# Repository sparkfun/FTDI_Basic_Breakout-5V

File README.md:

SparkFun FTDI Basic Breakout-5V
===============================

[*SparkFun FTDI Basic Breakout-5V(DEV-09716)*](https://www.sparkfun.com/products/9716)

This is a basic breakout board for the FTDI FT232RL USB to serial IC. 
The pinout of this board matches the FTDI cable to work with official Arduino and cloned Arduino boards. 
It can also be used for general serial applications. The major difference with this board is that it brings out the DTR pin as opposed to the RTS pin of the FTDI cable. 
The DTR pin allows an Arduino target to auto-reset when a new Sketch is downloaded. This is a really nice feature to have and allows a sketch to be downloaded without having to hit the reset button. 
This board will auto reset any Arduino board that has the reset pin brought out to a 6-pin connector.

Repository Contents
-------------------
* **/Hardware** - All Eagle design files (.brd, .sch)
* **/Production** - Test bed files and production panel files

Documentation
--------------

* **[Fritzing Part](https://github.com/sparkfun/Fritzing_Parts/blob/main/products/9716_sfe_ftdi_basic_breakout_5V_ft232rl.fzpz)** - Fritzing diagrams for SparkFun products.
* **[3D Model](https://github.com/sparkfun/3D_Models/tree/master/products/9716)**
* **[USB to Serial UART Boards Hookup Guide](https://learn.sparkfun.com/tutorials/sparkfun-usb-to-serial-uart-boards-hookup-guide)**
* **[How to Install FTDI Drivers](https://learn.sparkfun.com/tutorials/how-to-install-ftdi-drivers)**

 Product Versions
----------------
* [DEV-09716](https://www.sparkfun.com/products/9716)- 5V FTDI Basic Breakout
* [DEV-09873](https://www.sparkfun.com/products/9873)- 3.3V FTDI Basic Breakout

License Information
-------------------
The hardware is released under [Creative Commons ShareAlike 4.0 International](https://creativecommons.org/licenses/by-sa/4.0/).

Distributed as-is; no warranty is given.

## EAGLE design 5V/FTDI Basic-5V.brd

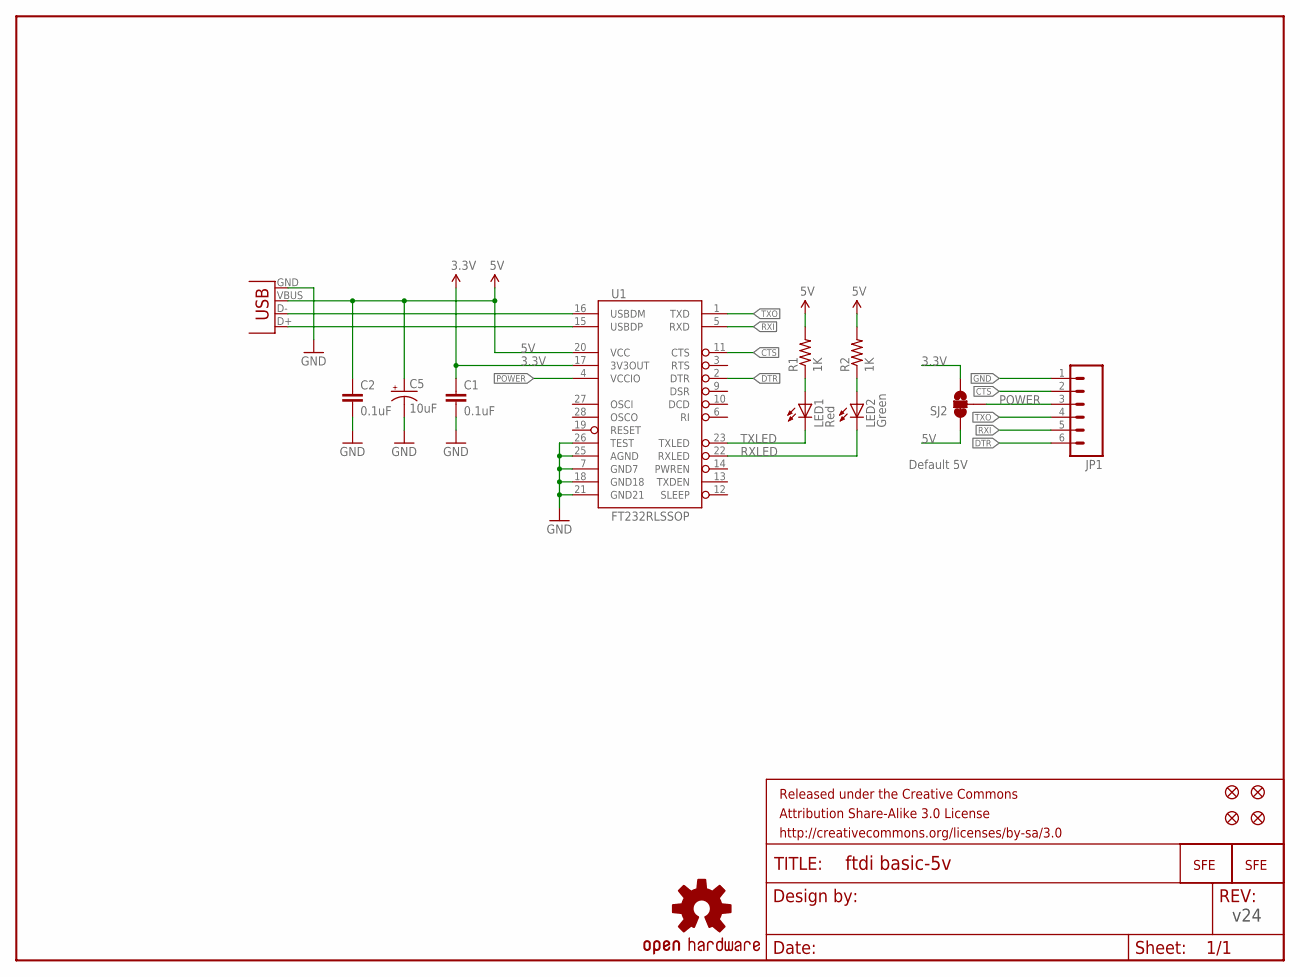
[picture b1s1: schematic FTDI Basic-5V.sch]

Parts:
C1, C2: 0.1uF; 0603-CAP
C5: 10uF; EIA3216
FRAME1: FRAME-LETTER; CREATIVE_COMMONS
JP1: M06SMD-FEMALE-V2; 1X06-SMD-FEMALE-V2
JP2: LOGO-SFESK; SFE-LOGO-FLAME
JP3, JP4, JP5, JP6: FIDUCIAL1X2; FIDUCIAL-1X2
LED1: Red; LED-0603
LED2: Green; LED-0603
LOGO1: OSHW-LOGOS; OSHW-LOGO-S
R1, R2: 1K; 0603-RES
SJ2: SOLDERJUMPER_2WAYS; SJ_3
U1: FT232RLSSOP; SSOP28DB
U$2: LOGO-SFENW2; SFE-NEW-WEB
X2: USB-SMD-NS; USB-MINIB-NOSTOP

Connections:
3.3V: C1.1, SJ2.3, U1.17 (3V3OUT)
5V: C2.1, C5.A (+), R1.2, R2.2, SJ2.1, U1.20 (VCC), X2.VBUS
CTS: JP1.2, U1.11 (CTS)
DTR: JP1.6, U1.2 (DTR)
GND: C1.2, C2.2, C5.C (-), JP1.1, U1.7 (GND7), U1.18 (GND18), U1.21 (GND21), U1.25 (AGND), U1.26 (TEST), X2.GND
unnamed: LED1.A, R1.1
unnamed: LED2.A, R2.1
POWER: JP1.3, SJ2.2, U1.4 (VCCIO)
RXI: JP1.5, U1.5 (RXD)
RXLED: LED2.C, U1.22 (RXLED)
TXLED: LED1.C, U1.23 (TXLED)
TXO: JP1.4, U1.1 (TXD)
USB_D+: U1.15 (USBDP), X2.D+
USB_D-: U1.16 (USBDM), X2.D-

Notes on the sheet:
Default 5V
v24

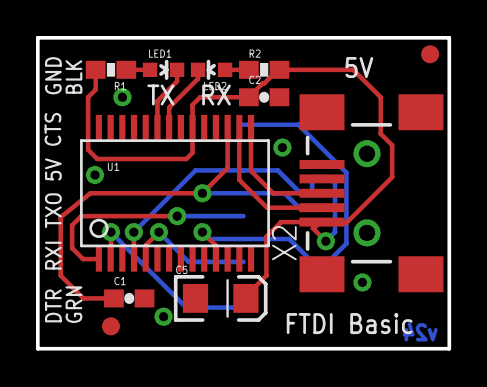
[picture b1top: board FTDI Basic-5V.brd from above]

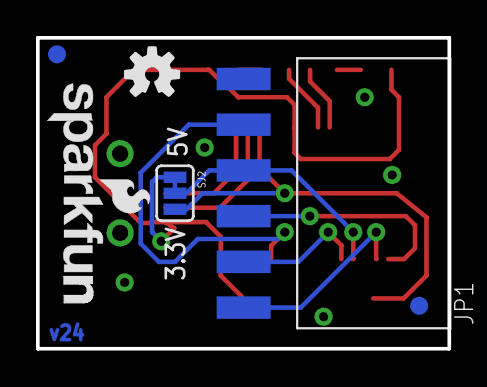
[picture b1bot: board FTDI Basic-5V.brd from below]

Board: 2 copper layers, 22.9 x 17.3 mm, 19 parts (7 on the bottom side), 14 nets.

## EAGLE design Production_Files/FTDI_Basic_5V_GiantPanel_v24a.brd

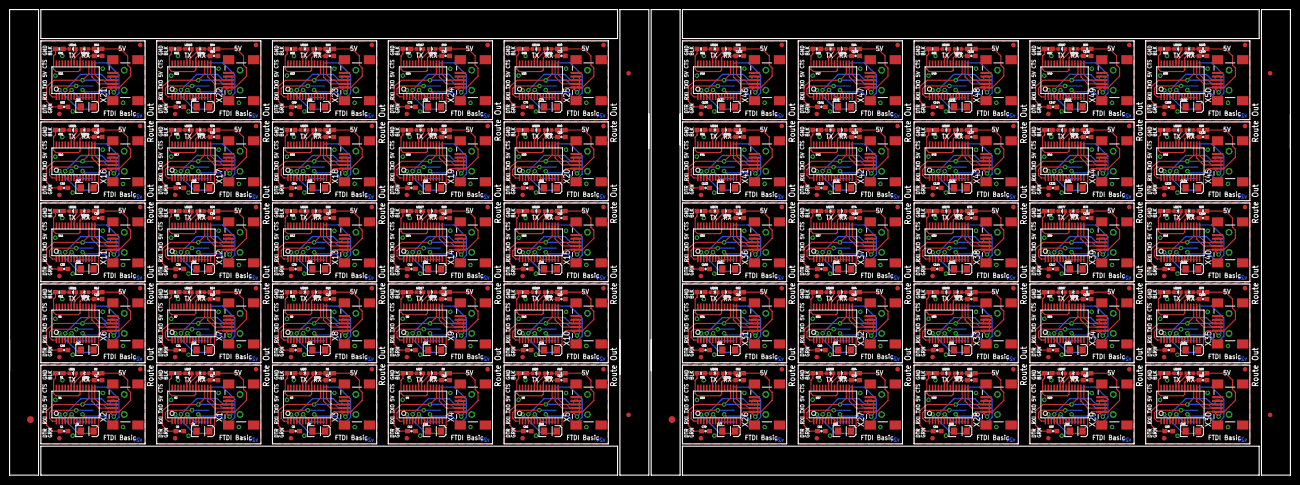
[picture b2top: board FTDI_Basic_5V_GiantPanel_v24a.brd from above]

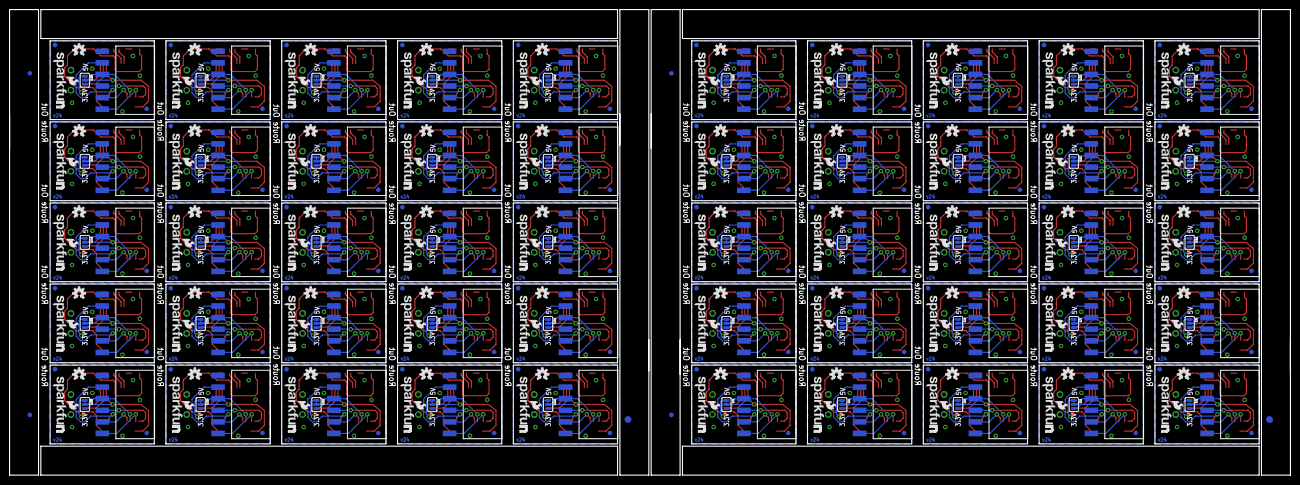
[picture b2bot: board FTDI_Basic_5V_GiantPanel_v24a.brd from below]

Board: 2 copper layers, 280.9 x 102.1 mm, 912 parts (356 on the bottom side), 700 nets.

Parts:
C1, C2, C3, C6, C7, C9, C10, C12, C13, C15, C16, C18, C19, C21, C22, C24, C25, C27, C28, C30, C31, C33, C34, C36, C37, C39, C40, C42, C43, C45, C46, C48, C49, C51, C52, C54, C55, C57, C58, C60, C61, C63, C64, C66, C67, C69, C70, C72, C73, C75, C76, C78, C79, C81, C82, C84, C85, C87, C88, C90, C91, C93, C94, C96, C97, C99, C100, C102, C103, C105, C106, C108, C109, C111, C112, C114, C115, C117, C118, C120, C121, C123, C124, C126, C127, C129, C130, C132, C133, C135, C136, C138, C139, C141, C142, C144, C145, C147, C148, C150: 0.1uF; 0603-CAP
C4, C5, C8, C11, C14, C17, C20, C23, C26, C29, C32, C35, C38, C41, C44, C47, C50, C53, C56, C59, C62, C65, C68, C71, C74, C77, C80, C83, C86, C89, C92, C95, C98, C101, C104, C107, C110, C113, C116, C119, C122, C125, C128, C131, C134, C137, C140, C143, C146, C149: 10uF; EIA3216
E$1, E$2, E$9, E$10: FIDUCIAL-1.5X3
E$3, E$4, E$5, E$6, E$7, E$8, E$11, E$12: FIDUCIAL-1X2
JP1, JP8, JP14, JP20, JP26, JP32, JP38, JP44, JP50, JP56, JP62, JP68, JP74, JP80, JP86, JP92, JP98, JP104, JP110, JP116, JP122, JP128, JP134, JP140, JP146, JP152, JP158, JP164, JP170, JP176, JP182, JP188, JP194, JP200, JP206, JP212, JP218, JP224, JP230, JP236, JP242, JP248, JP254, JP260, JP266, JP272, JP278, JP284, JP290, JP296: 1X06-SMD-FEMALE-V2
JP2, JP7, JP13, JP19, JP25, JP31, JP37, JP43, JP49, JP55, JP61, JP67, JP73, JP79, JP85, JP91, JP97, JP103, JP109, JP115, JP121, JP127, JP133, JP139, JP145, JP151, JP157, JP163, JP169, JP175, JP181, JP187, JP193, JP199, JP205, JP211, JP217, JP223, JP229, JP235, JP241, JP247, JP253, JP259, JP265, JP271, JP277, JP283, JP289, JP295: LOGO-SFESK; SFE-LOGO-FLAME
JP3, JP4, JP5, JP6, JP9, JP10, JP11, JP12, JP15, JP16, JP17, JP18, JP21, JP22, JP23, JP24, JP27, JP28, JP29, JP30, JP33, JP34, JP35, JP36, JP39, JP40, JP41, JP42, JP45, JP46, JP47, JP48, JP51, JP52, JP53, JP54, JP57, JP58, JP59, JP60, JP63, JP64, JP65, JP66, JP69, JP70, JP71, JP72, JP75, JP76, JP77, JP78, JP81, JP82, JP83, JP84, JP87, JP88, JP89, JP90, JP93, JP94, JP95, JP96, JP99, JP100, JP101, JP102, JP105, JP106, JP107, JP108, JP111, JP112, JP113, JP114, JP117, JP118, JP119, JP120, JP123, JP124, JP125, JP126, JP129, JP130, JP131, JP132, JP135, JP136, JP137, JP138, JP141, JP142, JP143, JP144, JP147, JP148, JP149, JP150, JP153, JP154, JP155, JP156, JP159, JP160, JP161, JP162, JP165, JP166, JP167, JP168, JP171, JP172, JP173, JP174, JP177, JP178, JP179, JP180, JP183, JP184, JP185, JP186, JP189, JP190, JP191, JP192, JP195, JP196, JP197, JP198, JP201, JP202, JP203, JP204, JP207, JP208, JP209, JP210, JP213, JP214, JP215, JP216, JP219, JP220, JP221, JP222, JP225, JP226, JP227, JP228, JP231, JP232, JP233, JP234, JP237, JP238, JP239, JP240, JP243, JP244, JP245, JP246, JP249, JP250, JP251, JP252, JP255, JP256, JP257, JP258, JP261, JP262, JP263, JP264, JP267, JP268, JP269, JP270, JP273, JP274, JP275, JP276, JP279, JP280, JP281, JP282, JP285, JP286, JP287, JP288, JP291, JP292, JP293, JP294, JP297, JP298, JP299, JP300: FIDUCIAL1X2; FIDUCIAL-1X2
LED1, LED3, LED5, LED7, LED9, LED11, LED13, LED15, LED17, LED19, LED21, LED23, LED25, LED27, LED29, LED31, LED33, LED35, LED37, LED39, LED41, LED43, LED45, LED47, LED49, LED51, LED53, LED55, LED57, LED59, LED61, LED63, LED65, LED67, LED69, LED71, LED73, LED75, LED77, LED79, LED81, LED83, LED85, LED87, LED89, LED91, LED93, LED95, LED97, LED99: Red; LED-0603
LED2, LED4, LED6, LED8, LED10, LED12, LED14, LED16, LED18, LED20, LED22, LED24, LED26, LED28, LED30, LED32, LED34, LED36, LED38, LED40, LED42, LED44, LED46, LED48, LED50, LED52, LED54, LED56, LED58, LED60, LED62, LED64, LED66, LED68, LED70, LED72, LED74, LED76, LED78, LED80, LED82, LED84, LED86, LED88, LED90, LED92, LED94, LED96, LED98, LED100: Green; LED-0603
LOGO1, LOGO2, LOGO3, LOGO4, LOGO5, LOGO6, LOGO7, LOGO8, LOGO9, LOGO10, LOGO11, LOGO12, LOGO13, LOGO14, LOGO15, LOGO16, LOGO17, LOGO18, LOGO19, LOGO20, LOGO21, LOGO22, LOGO23, LOGO24, LOGO25, LOGO26, LOGO27, LOGO28, LOGO29, LOGO30, LOGO31, LOGO32, LOGO33, LOGO34, LOGO35, LOGO36, LOGO37, LOGO38, LOGO39, LOGO40, LOGO41, LOGO42, LOGO43, LOGO44, LOGO45, LOGO46, LOGO47, LOGO48, LOGO49, LOGO50: OSHW-LOGOS; OSHW-LOGO-S
R1, R2, R3, R4, R5, R6, R7, R8, R9, R10, R11, R12, R13, R14, R15, R16, R17, R18, R19, R20, R21, R22, R23, R24, R25, R26, R27, R28, R29, R30, R31, R32, R33, R34, R35, R36, R37, R38, R39, R40, R41, R42, R43, R44, R45, R46, R47, R48, R49, R50, R51, R52, R53, R54, R55, R56, R57, R58, R59, R60, R61, R62, R63, R64, R65, R66, R67, R68, R69, R70, R71, R72, R73, R74, R75, R76, R77, R78, R79, R80, R81, R82, R83, R84, R85, R86, R87, R88, R89, R90, R91, R92, R93, R94, R95, R96, R97, R98, R99, R100: 1K; 0603-RES
SJ1, SJ2, SJ3, SJ4, SJ5, SJ6, SJ7, SJ8, SJ9, SJ10, SJ11, SJ12, SJ13, SJ14, SJ15, SJ16, SJ17, SJ18, SJ19, SJ20, SJ21, SJ22, SJ23, SJ24, SJ25, SJ26, SJ27, SJ28, SJ29, SJ30, SJ31, SJ32, SJ33, SJ34, SJ35, SJ36, SJ37, SJ38, SJ39, SJ40, SJ41, SJ42, SJ43, SJ44, SJ45, SJ46, SJ47, SJ48, SJ49, SJ50: SJ_3
U1, U2, U3, U4, U5, U6, U7, U8, U9, U10, U11, U12, U13, U14, U15, U16, U17, U18, U19, U20, U21, U22, U23, U24, U25, U26, U27, U28, U29, U30, U31, U32, U33, U34, U35, U36, U37, U38, U39, U40, U41, U42, U43, U44, U45, U46, U47, U48, U49, U50: FT232RLSSOP; SSOP28DB
U$1, U$2, U$3, U$4, U$5, U$6, U$7, U$8, U$9, U$10, U$11, U$12, U$13, U$14, U$15, U$16, U$17, U$18, U$19, U$20, U$21, U$22, U$23, U$24, U$25, U$26, U$27, U$28, U$29, U$30, U$31, U$32, U$33, U$34, U$35, U$36, U$37, U$38, U$39, U$40, U$41, U$42, U$43, U$44, U$45, U$46, U$47, U$48, U$49, U$50: LOGO-SFENW2; SFE-NEW-WEB
X1, X2, X3, X4, X5, X6, X7, X8, X9, X10, X11, X12, X13, X14, X15, X16, X17, X18, X19, X20, X21, X22, X23, X24, X25, X26, X27, X28, X29, X30, X31, X32, X33, X34, X35, X36, X37, X38, X39, X40, X41, X42, X43, X44, X45, X46, X47, X48, X49, X50: USB-SMD-NS; USB-MINIB-NOSTOP

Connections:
3.3V: C1.1, SJ2.3, U1.17
3.3V1: C6.1, SJ1.3, U2.17
3.3V2: C9.1, SJ3.3, U3.17
3.3V3: C12.1, SJ4.3, U4.17
3.3V4: C15.1, SJ5.3, U5.17
3.3V5: C18.1, SJ6.3, U6.17
3.3V6: C21.1, SJ7.3, U7.17
3.3V7: C24.1, SJ8.3, U8.17
3.3V8: C27.1, SJ9.3, U9.17
3.3V9: C30.1, SJ10.3, U10.17
3.3V10: C33.1, SJ11.3, U11.17
3.3V11: C36.1, SJ12.3, U12.17
3.3V12: C39.1, SJ13.3, U13.17
3.3V13: C42.1, SJ14.3, U14.17
3.3V14: C45.1, SJ15.3, U15.17
3.3V15: C48.1, SJ16.3, U16.17
3.3V16: C51.1, SJ17.3, U17.17
3.3V17: C54.1, SJ18.3, U18.17
3.3V18: C57.1, SJ19.3, U19.17
3.3V19: C60.1, SJ20.3, U20.17
3.3V20: C63.1, SJ21.3, U21.17
3.3V21: C66.1, SJ22.3, U22.17
3.3V22: C69.1, SJ23.3, U23.17
3.3V23: C72.1, SJ24.3, U24.17
3.3V24: C75.1, SJ25.3, U25.17
3.3V25: C78.1, SJ26.3, U26.17
3.3V26: C81.1, SJ27.3, U27.17
3.3V27: C84.1, SJ28.3, U28.17
3.3V28: C87.1, SJ29.3, U29.17
3.3V29: C90.1, SJ30.3, U30.17
3.3V30: C93.1, SJ31.3, U31.17
3.3V31: C96.1, SJ32.3, U32.17
3.3V32: C99.1, SJ33.3, U33.17
3.3V33: C102.1, SJ34.3, U34.17
3.3V34: C105.1, SJ35.3, U35.17
3.3V35: C108.1, SJ36.3, U36.17
3.3V36: C111.1, SJ37.3, U37.17
3.3V37: C114.1, SJ38.3, U38.17
3.3V38: C117.1, SJ39.3, U39.17
3.3V39: C120.1, SJ40.3, U40.17
3.3V40: C123.1, SJ41.3, U41.17
3.3V41: C126.1, SJ42.3, U42.17
3.3V42: C129.1, SJ43.3, U43.17
3.3V43: C132.1, SJ44.3, U44.17
3.3V44: C135.1, SJ45.3, U45.17
3.3V45: C138.1, SJ46.3, U46.17
3.3V46: C141.1, SJ47.3, U47.17
3.3V47: C144.1, SJ48.3, U48.17
3.3V48: C147.1, SJ49.3, U49.17
3.3V49: C150.1, SJ50.3, U50.17
5V: C2.1, C5.A, R1.2, R2.2, SJ2.1, U1.20, X2.VBUS
5V1: C3.1, C4.A, R3.2, R4.2, SJ1.1, U2.20, X1.VBUS
5V2: C7.1, C8.A, R5.2, R6.2, SJ3.1, U3.20, X3.VBUS
5V3: C10.1, C11.A, R7.2, R8.2, SJ4.1, U4.20, X4.VBUS
5V4: C13.1, C14.A, R9.2, R10.2, SJ5.1, U5.20, X5.VBUS
5V5: C16.1, C17.A, R11.2, R12.2, SJ6.1, U6.20, X6.VBUS
5V6: C19.1, C20.A, R13.2, R14.2, SJ7.1, U7.20, X7.VBUS
5V7: C22.1, C23.A, R15.2, R16.2, SJ8.1, U8.20, X8.VBUS
5V8: C25.1, C26.A, R17.2, R18.2, SJ9.1, U9.20, X9.VBUS
5V9: C28.1, C29.A, R19.2, R20.2, SJ10.1, U10.20, X10.VBUS
5V10: C31.1, C32.A, R21.2, R22.2, SJ11.1, U11.20, X11.VBUS
5V11: C34.1, C35.A, R23.2, R24.2, SJ12.1, U12.20, X12.VBUS
5V12: C37.1, C38.A, R25.2, R26.2, SJ13.1, U13.20, X13.VBUS
5V13: C40.1, C41.A, R27.2, R28.2, SJ14.1, U14.20, X14.VBUS
5V14: C43.1, C44.A, R29.2, R30.2, SJ15.1, U15.20, X15.VBUS
5V15: C46.1, C47.A, R31.2, R32.2, SJ16.1, U16.20, X16.VBUS
5V16: C49.1, C50.A, R33.2, R34.2, SJ17.1, U17.20, X17.VBUS
5V17: C52.1, C53.A, R35.2, R36.2, SJ18.1, U18.20, X18.VBUS
5V18: C55.1, C56.A, R37.2, R38.2, SJ19.1, U19.20, X19.VBUS
5V19: C58.1, C59.A, R39.2, R40.2, SJ20.1, U20.20, X20.VBUS
5V20: C61.1, C62.A, R41.2, R42.2, SJ21.1, U21.20, X21.VBUS
5V21: C64.1, C65.A, R43.2, R44.2, SJ22.1, U22.20, X22.VBUS
5V22: C67.1, C68.A, R45.2, R46.2, SJ23.1, U23.20, X23.VBUS
5V23: C70.1, C71.A, R47.2, R48.2, SJ24.1, U24.20, X24.VBUS
5V24: C73.1, C74.A, R49.2, R50.2, SJ25.1, U25.20, X25.VBUS
5V25: C76.1, C77.A, R51.2, R52.2, SJ26.1, U26.20, X26.VBUS
5V26: C79.1, C80.A, R53.2, R54.2, SJ27.1, U27.20, X27.VBUS
5V27: C82.1, C83.A, R55.2, R56.2, SJ28.1, U28.20, X28.VBUS
5V28: C85.1, C86.A, R57.2, R58.2, SJ29.1, U29.20, X29.VBUS
5V29: C88.1, C89.A, R59.2, R60.2, SJ30.1, U30.20, X30.VBUS
5V30: C91.1, C92.A, R61.2, R62.2, SJ31.1, U31.20, X31.VBUS
5V31: C94.1, C95.A, R63.2, R64.2, SJ32.1, U32.20, X32.VBUS
5V32: C97.1, C98.A, R65.2, R66.2, SJ33.1, U33.20, X33.VBUS
5V33: C100.1, C101.A, R67.2, R68.2, SJ34.1, U34.20, X34.VBUS
5V34: C103.1, C104.A, R69.2, R70.2, SJ35.1, U35.20, X35.VBUS
5V35: C106.1, C107.A, R71.2, R72.2, SJ36.1, U36.20, X36.VBUS
5V36: C109.1, C110.A, R73.2, R74.2, SJ37.1, U37.20, X37.VBUS
5V37: C112.1, C113.A, R75.2, R76.2, SJ38.1, U38.20, X38.VBUS
5V38: C115.1, C116.A, R77.2, R78.2, SJ39.1, U39.20, X39.VBUS
5V39: C118.1, C119.A, R79.2, R80.2, SJ40.1, U40.20, X40.VBUS
5V40: C121.1, C122.A, R81.2, R82.2, SJ41.1, U41.20, X41.VBUS
5V41: C124.1, C125.A, R83.2, R84.2, SJ42.1, U42.20, X42.VBUS
5V42: C127.1, C128.A, R85.2, R86.2, SJ43.1, U43.20, X43.VBUS
5V43: C130.1, C131.A, R87.2, R88.2, SJ44.1, U44.20, X44.VBUS
5V44: C133.1, C134.A, R89.2, R90.2, SJ45.1, U45.20, X45.VBUS
5V45: C136.1, C137.A, R91.2, R92.2, SJ46.1, U46.20, X46.VBUS
5V46: C139.1, C140.A, R93.2, R94.2, SJ47.1, U47.20, X47.VBUS
5V47: C142.1, C143.A, R95.2, R96.2, SJ48.1, U48.20, X48.VBUS
5V48: C145.1, C146.A, R97.2, R98.2, SJ49.1, U49.20, X49.VBUS
5V49: C148.1, C149.A, R99.2, R100.2, SJ50.1, U50.20, X50.VBUS
CTS: JP1.2, U1.11
CTS1: JP8.2, U2.11
CTS2: JP14.2, U3.11
CTS3: JP20.2, U4.11
CTS4: JP26.2, U5.11
CTS5: JP32.2, U6.11
CTS6: JP38.2, U7.11
CTS7: JP44.2, U8.11
CTS8: JP50.2, U9.11
CTS9: JP56.2, U10.11
CTS10: JP62.2, U11.11
CTS11: JP68.2, U12.11
CTS12: JP74.2, U13.11
CTS13: JP80.2, U14.11
CTS14: JP86.2, U15.11
CTS15: JP92.2, U16.11
CTS16: JP98.2, U17.11
CTS17: JP104.2, U18.11
CTS18: JP110.2, U19.11
CTS19: JP116.2, U20.11
CTS20: JP122.2, U21.11
CTS21: JP128.2, U22.11
CTS22: JP134.2, U23.11
CTS23: JP140.2, U24.11
CTS24: JP146.2, U25.11
CTS25: JP152.2, U26.11
CTS26: JP158.2, U27.11
CTS27: JP164.2, U28.11
CTS28: JP170.2, U29.11
CTS29: JP176.2, U30.11
CTS30: JP182.2, U31.11
CTS31: JP188.2, U32.11
CTS32: JP194.2, U33.11
CTS33: JP200.2, U34.11
CTS34: JP206.2, U35.11
CTS35: JP212.2, U36.11
CTS36: JP218.2, U37.11
CTS37: JP224.2, U38.11
CTS38: JP230.2, U39.11
CTS39: JP236.2, U40.11
CTS40: JP242.2, U41.11
CTS41: JP248.2, U42.11
CTS42: JP254.2, U43.11
CTS43: JP260.2, U44.11
CTS44: JP266.2, U45.11
CTS45: JP272.2, U46.11
CTS46: JP278.2, U47.11
CTS47: JP284.2, U48.11
CTS48: JP290.2, U49.11
CTS49: JP296.2, U50.11
DTR: JP1.6, U1.2
DTR1: JP8.6, U2.2
DTR2: JP14.6, U3.2
DTR3: JP20.6, U4.2
DTR4: JP26.6, U5.2
DTR5: JP32.6, U6.2
DTR6: JP38.6, U7.2
DTR7: JP44.6, U8.2
DTR8: JP50.6, U9.2
DTR9: JP56.6, U10.2
DTR10: JP62.6, U11.2
DTR11: JP68.6, U12.2
DTR12: JP74.6, U13.2
DTR13: JP80.6, U14.2
DTR14: JP86.6, U15.2
DTR15: JP92.6, U16.2
DTR16: JP98.6, U17.2
DTR17: JP104.6, U18.2
DTR18: JP110.6, U19.2
DTR19: JP116.6, U20.2
DTR20: JP122.6, U21.2
DTR21: JP128.6, U22.2
DTR22: JP134.6, U23.2
DTR23: JP140.6, U24.2
DTR24: JP146.6, U25.2
DTR25: JP152.6, U26.2
DTR26: JP158.6, U27.2
DTR27: JP164.6, U28.2
DTR28: JP170.6, U29.2
DTR29: JP176.6, U30.2
DTR30: JP182.6, U31.2
DTR31: JP188.6, U32.2
DTR32: JP194.6, U33.2
DTR33: JP200.6, U34.2
DTR34: JP206.6, U35.2
DTR35: JP212.6, U36.2
DTR36: JP218.6, U37.2
DTR37: JP224.6, U38.2
DTR38: JP230.6, U39.2
DTR39: JP236.6, U40.2
DTR40: JP242.6, U41.2
DTR41: JP248.6, U42.2
DTR42: JP254.6, U43.2
DTR43: JP260.6, U44.2
DTR44: JP266.6, U45.2
DTR45: JP272.6, U46.2
DTR46: JP278.6, U47.2
DTR47: JP284.6, U48.2
DTR48: JP290.6, U49.2
DTR49: JP296.6, U50.2
GND: C1.2, C2.2, C5.C, JP1.1, U1.7, U1.18, U1.21, U1.25, U1.26, X2.GND
GND1: C3.2, C4.C, C6.2, JP8.1, U2.7, U2.18, U2.21, U2.25, U2.26, X1.GND
GND2: C7.2, C8.C, C9.2, JP14.1, U3.7, U3.18, U3.21, U3.25, U3.26, X3.GND
GND3: C10.2, C11.C, C12.2, JP20.1, U4.7, U4.18, U4.21, U4.25, U4.26, X4.GND
GND4: C13.2, C14.C, C15.2, JP26.1, U5.7, U5.18, U5.21, U5.25, U5.26, X5.GND
GND5: C16.2, C17.C, C18.2, JP32.1, U6.7, U6.18, U6.21, U6.25, U6.26, X6.GND
GND6: C19.2, C20.C, C21.2, JP38.1, U7.7, U7.18, U7.21, U7.25, U7.26, X7.GND
GND7: C22.2, C23.C, C24.2, JP44.1, U8.7, U8.18, U8.21, U8.25, U8.26, X8.GND
GND8: C25.2, C26.C, C27.2, JP50.1, U9.7, U9.18, U9.21, U9.25, U9.26, X9.GND
GND9: C28.2, C29.C, C30.2, JP56.1, U10.7, U10.18, U10.21, U10.25, U10.26, X10.GND
GND10: C31.2, C32.C, C33.2, JP62.1, U11.7, U11.18, U11.21, U11.25, U11.26, X11.GND
GND11: C34.2, C35.C, C36.2, JP68.1, U12.7, U12.18, U12.21, U12.25, U12.26, X12.GND
GND12: C37.2, C38.C, C39.2, JP74.1, U13.7, U13.18, U13.21, U13.25, U13.26, X13.GND
GND13: C40.2, C41.C, C42.2, JP80.1, U14.7, U14.18, U14.21, U14.25, U14.26, X14.GND
GND14: C43.2, C44.C, C45.2, JP86.1, U15.7, U15.18, U15.21, U15.25, U15.26, X15.GND
GND15: C46.2, C47.C, C48.2, JP92.1, U16.7, U16.18, U16.21, U16.25, U16.26, X16.GND
GND16: C49.2, C50.C, C51.2, JP98.1, U17.7, U17.18, U17.21, U17.25, U17.26, X17.GND
GND17: C52.2, C53.C, C54.2, JP104.1, U18.7, U18.18, U18.21, U18.25, U18.26, X18.GND
GND18: C55.2, C56.C, C57.2, JP110.1, U19.7, U19.18, U19.21, U19.25, U19.26, X19.GND
GND19: C58.2, C59.C, C60.2, JP116.1, U20.7, U20.18, U20.21, U20.25, U20.26, X20.GND
GND20: C61.2, C62.C, C63.2, JP122.1, U21.7, U21.18, U21.21, U21.25, U21.26, X21.GND
GND21: C64.2, C65.C, C66.2, JP128.1, U22.7, U22.18, U22.21, U22.25, U22.26, X22.GND
GND22: C67.2, C68.C, C69.2, JP134.1, U23.7, U23.18, U23.21, U23.25, U23.26, X23.GND
GND23: C70.2, C71.C, C72.2, JP140.1, U24.7, U24.18, U24.21, U24.25, U24.26, X24.GND
GND24: C73.2, C74.C, C75.2, JP146.1, U25.7, U25.18, U25.21, U25.25, U25.26, X25.GND
GND25: C76.2, C77.C, C78.2, JP152.1, U26.7, U26.18, U26.21, U26.25, U26.26, X26.GND
GND26: C79.2, C80.C, C81.2, JP158.1, U27.7, U27.18, U27.21, U27.25, U27.26, X27.GND
GND27: C82.2, C83.C, C84.2, JP164.1, U28.7, U28.18, U28.21, U28.25, U28.26, X28.GND
GND28: C85.2, C86.C, C87.2, JP170.1, U29.7, U29.18, U29.21, U29.25, U29.26, X29.GND
GND29: C88.2, C89.C, C90.2, JP176.1, U30.7, U30.18, U30.21, U30.25, U30.26, X30.GND
GND30: C91.2, C92.C, C93.2, JP182.1, U31.7, U31.18, U31.21, U31.25, U31.26, X31.GND
GND31: C94.2, C95.C, C96.2, JP188.1, U32.7, U32.18, U32.21, U32.25, U32.26, X32.GND
GND32: C97.2, C98.C, C99.2, JP194.1, U33.7, U33.18, U33.21, U33.25, U33.26, X33.GND
GND33: C100.2, C101.C, C102.2, JP200.1, U34.7, U34.18, U34.21, U34.25, U34.26, X34.GND
GND34: C103.2, C104.C, C105.2, JP206.1, U35.7, U35.18, U35.21, U35.25, U35.26, X35.GND
GND35: C106.2, C107.C, C108.2, JP212.1, U36.7, U36.18, U36.21, U36.25, U36.26, X36.GND
GND36: C109.2, C110.C, C111.2, JP218.1, U37.7, U37.18, U37.21, U37.25, U37.26, X37.GND
GND37: C112.2, C113.C, C114.2, JP224.1, U38.7, U38.18, U38.21, U38.25, U38.26, X38.GND
GND38: C115.2, C116.C, C117.2, JP230.1, U39.7, U39.18, U39.21, U39.25, U39.26, X39.GND
GND39: C118.2, C119.C, C120.2, JP236.1, U40.7, U40.18, U40.21, U40.25, U40.26, X40.GND
GND40: C121.2, C122.C, C123.2, JP242.1, U41.7, U41.18, U41.21, U41.25, U41.26, X41.GND
GND41: C124.2, C125.C, C126.2, JP248.1, U42.7, U42.18, U42.21, U42.25, U42.26, X42.GND
GND42: C127.2, C128.C, C129.2, JP254.1, U43.7, U43.18, U43.21, U43.25, U43.26, X43.GND
GND43: C130.2, C131.C, C132.2, JP260.1, U44.7, U44.18, U44.21, U44.25, U44.26, X44.GND
GND44: C133.2, C134.C, C135.2, JP266.1, U45.7, U45.18, U45.21, U45.25, U45.26, X45.GND
GND45: C136.2, C137.C, C138.2, JP272.1, U46.7, U46.18, U46.21, U46.25, U46.26, X46.GND
GND46: C139.2, C140.C, C141.2, JP278.1, U47.7, U47.18, U47.21, U47.25, U47.26, X47.GND
GND47: C142.2, C143.C, C144.2, JP284.1, U48.7, U48.18, U48.21, U48.25, U48.26, X48.GND
GND48: C145.2, C146.C, C147.2, JP290.1, U49.7, U49.18, U49.21, U49.25, U49.26, X49.GND
GND49: C148.2, C149.C, C150.2, JP296.1, U50.7, U50.18, U50.21, U50.25, U50.26, X50.GND
unnamed: LED1.A, R1.1
unnamed: LED2.A, R2.1
unnamed: LED3.A, R3.1
unnamed: LED4.A, R4.1
unnamed: LED5.A, R5.1
unnamed: LED6.A, R6.1
unnamed: LED7.A, R7.1
unnamed: LED8.A, R8.1
unnamed: LED9.A, R9.1
unnamed: LED10.A, R10.1
unnamed: LED11.A, R11.1
unnamed: LED12.A, R12.1
unnamed: LED13.A, R13.1
unnamed: LED14.A, R14.1
unnamed: LED15.A, R15.1
unnamed: LED16.A, R16.1
unnamed: LED17.A, R17.1
unnamed: LED18.A, R18.1
unnamed: LED19.A, R19.1
unnamed: LED20.A, R20.1
unnamed: LED21.A, R21.1
unnamed: LED22.A, R22.1
unnamed: LED23.A, R23.1
unnamed: LED24.A, R24.1
unnamed: LED25.A, R25.1
unnamed: LED26.A, R26.1
unnamed: LED27.A, R27.1
unnamed: LED28.A, R28.1
unnamed: LED29.A, R29.1
unnamed: LED30.A, R30.1
unnamed: LED31.A, R31.1
unnamed: LED32.A, R32.1
unnamed: LED33.A, R33.1
unnamed: LED34.A, R34.1
unnamed: LED35.A, R35.1
unnamed: LED36.A, R36.1
unnamed: LED37.A, R37.1
unnamed: LED38.A, R38.1
unnamed: LED39.A, R39.1
unnamed: LED40.A, R40.1
unnamed: LED41.A, R41.1
unnamed: LED42.A, R42.1
unnamed: LED43.A, R43.1
unnamed: LED44.A, R44.1
unnamed: LED45.A, R45.1
unnamed: LED46.A, R46.1
unnamed: LED47.A, R47.1
unnamed: LED48.A, R48.1
unnamed: LED49.A, R49.1
unnamed: LED50.A, R50.1
unnamed: LED51.A, R51.1
unnamed: LED52.A, R52.1
unnamed: LED53.A, R53.1
unnamed: LED54.A, R54.1
unnamed: LED55.A, R55.1
unnamed: LED56.A, R56.1
unnamed: LED57.A, R57.1
unnamed: LED58.A, R58.1
unnamed: LED59.A, R59.1
unnamed: LED60.A, R60.1
unnamed: LED61.A, R61.1
unnamed: LED62.A, R62.1
unnamed: LED63.A, R63.1
unnamed: LED64.A, R64.1
unnamed: LED65.A, R65.1
unnamed: LED66.A, R66.1
unnamed: LED67.A, R67.1
unnamed: LED68.A, R68.1
unnamed: LED69.A, R69.1
unnamed: LED70.A, R70.1
unnamed: LED71.A, R71.1
unnamed: LED72.A, R72.1
unnamed: LED73.A, R73.1
unnamed: LED74.A, R74.1
unnamed: LED75.A, R75.1
unnamed: LED76.A, R76.1
unnamed: LED77.A, R77.1
unnamed: LED78.A, R78.1
unnamed: LED79.A, R79.1
unnamed: LED80.A, R80.1
unnamed: LED81.A, R81.1
unnamed: LED82.A, R82.1
unnamed: LED83.A, R83.1
unnamed: LED84.A, R84.1
unnamed: LED85.A, R85.1
unnamed: LED86.A, R86.1
unnamed: LED87.A, R87.1
unnamed: LED88.A, R88.1
unnamed: LED89.A, R89.1
unnamed: LED90.A, R90.1
unnamed: LED91.A, R91.1
unnamed: LED92.A, R92.1
unnamed: LED93.A, R93.1
unnamed: LED94.A, R94.1
unnamed: LED95.A, R95.1
unnamed: LED96.A, R96.1
unnamed: LED97.A, R97.1
unnamed: LED98.A, R98.1
unnamed: LED99.A, R99.1
unnamed: LED100.A, R100.1
POWER: JP1.3, SJ2.2, U1.4
POWER1: JP8.3, SJ1.2, U2.4
POWER2: JP14.3, SJ3.2, U3.4
POWER3: JP20.3, SJ4.2, U4.4
POWER4: JP26.3, SJ5.2, U5.4
POWER5: JP32.3, SJ6.2, U6.4
POWER6: JP38.3, SJ7.2, U7.4
POWER7: JP44.3, SJ8.2, U8.4
POWER8: JP50.3, SJ9.2, U9.4
POWER9: JP56.3, SJ10.2, U10.4
POWER10: JP62.3, SJ11.2, U11.4
POWER11: JP68.3, SJ12.2, U12.4
POWER12: JP74.3, SJ13.2, U13.4
POWER13: JP80.3, SJ14.2, U14.4
POWER14: JP86.3, SJ15.2, U15.4
POWER15: JP92.3, SJ16.2, U16.4
POWER16: JP98.3, SJ17.2, U17.4
POWER17: JP104.3, SJ18.2, U18.4
POWER18: JP110.3, SJ19.2, U19.4
POWER19: JP116.3, SJ20.2, U20.4
POWER20: JP122.3, SJ21.2, U21.4
POWER21: JP128.3, SJ22.2, U22.4
POWER22: JP134.3, SJ23.2, U23.4
POWER23: JP140.3, SJ24.2, U24.4
POWER24: JP146.3, SJ25.2, U25.4
POWER25: JP152.3, SJ26.2, U26.4
POWER26: JP158.3, SJ27.2, U27.4
POWER27: JP164.3, SJ28.2, U28.4
POWER28: JP170.3, SJ29.2, U29.4
POWER29: JP176.3, SJ30.2, U30.4
POWER30: JP182.3, SJ31.2, U31.4
POWER31: JP188.3, SJ32.2, U32.4
POWER32: JP194.3, SJ33.2, U33.4
POWER33: JP200.3, SJ34.2, U34.4
POWER34: JP206.3, SJ35.2, U35.4
POWER35: JP212.3, SJ36.2, U36.4
POWER36: JP218.3, SJ37.2, U37.4
POWER37: JP224.3, SJ38.2, U38.4
POWER38: JP230.3, SJ39.2, U39.4
POWER39: JP236.3, SJ40.2, U40.4
POWER40: JP242.3, SJ41.2, U41.4
POWER41: JP248.3, SJ42.2, U42.4
POWER42: JP254.3, SJ43.2, U43.4
POWER43: JP260.3, SJ44.2, U44.4
POWER44: JP266.3, SJ45.2, U45.4
POWER45: JP272.3, SJ46.2, U46.4
POWER46: JP278.3, SJ47.2, U47.4
POWER47: JP284.3, SJ48.2, U48.4
POWER48: JP290.3, SJ49.2, U49.4
POWER49: JP296.3, SJ50.2, U50.4
RXI: JP1.5, U1.5
RXI1: JP8.5, U2.5
RXI2: JP14.5, U3.5
RXI3: JP20.5, U4.5
RXI4: JP26.5, U5.5
RXI5: JP32.5, U6.5
RXI6: JP38.5, U7.5
RXI7: JP44.5, U8.5
RXI8: JP50.5, U9.5
RXI9: JP56.5, U10.5
RXI10: JP62.5, U11.5
RXI11: JP68.5, U12.5
RXI12: JP74.5, U13.5
RXI13: JP80.5, U14.5
RXI14: JP86.5, U15.5
RXI15: JP92.5, U16.5
RXI16: JP98.5, U17.5
RXI17: JP104.5, U18.5
RXI18: JP110.5, U19.5
RXI19: JP116.5, U20.5
RXI20: JP122.5, U21.5
RXI21: JP128.5, U22.5
RXI22: JP134.5, U23.5
RXI23: JP140.5, U24.5
RXI24: JP146.5, U25.5
RXI25: JP152.5, U26.5
RXI26: JP158.5, U27.5
RXI27: JP164.5, U28.5
RXI28: JP170.5, U29.5
RXI29: JP176.5, U30.5
RXI30: JP182.5, U31.5
RXI31: JP188.5, U32.5
RXI32: JP194.5, U33.5
RXI33: JP200.5, U34.5
RXI34: JP206.5, U35.5
RXI35: JP212.5, U36.5
RXI36: JP218.5, U37.5
RXI37: JP224.5, U38.5
RXI38: JP230.5, U39.5
RXI39: JP236.5, U40.5
RXI40: JP242.5, U41.5
RXI41: JP248.5, U42.5
RXI42: JP254.5, U43.5
RXI43: JP260.5, U44.5
RXI44: JP266.5, U45.5
RXI45: JP272.5, U46.5
RXI46: JP278.5, U47.5
RXI47: JP284.5, U48.5
RXI48: JP290.5, U49.5
RXI49: JP296.5, U50.5
RXLED: LED2.C, U1.22
RXLED1: LED4.C, U2.22
RXLED2: LED6.C, U3.22
RXLED3: LED8.C, U4.22
RXLED4: LED10.C, U5.22
RXLED5: LED12.C, U6.22
RXLED6: LED14.C, U7.22
RXLED7: LED16.C, U8.22
RXLED8: LED18.C, U9.22
RXLED9: LED20.C, U10.22
RXLED10: LED22.C, U11.22
RXLED11: LED24.C, U12.22
RXLED12: LED26.C, U13.22
RXLED13: LED28.C, U14.22
RXLED14: LED30.C, U15.22
RXLED15: LED32.C, U16.22
RXLED16: LED34.C, U17.22
RXLED17: LED36.C, U18.22
RXLED18: LED38.C, U19.22
RXLED19: LED40.C, U20.22
RXLED20: LED42.C, U21.22
RXLED21: LED44.C, U22.22
RXLED22: LED46.C, U23.22
RXLED23: LED48.C, U24.22
RXLED24: LED50.C, U25.22
RXLED25: LED52.C, U26.22
RXLED26: LED54.C, U27.22
RXLED27: LED56.C, U28.22
RXLED28: LED58.C, U29.22
RXLED29: LED60.C, U30.22
RXLED30: LED62.C, U31.22
RXLED31: LED64.C, U32.22
RXLED32: LED66.C, U33.22
RXLED33: LED68.C, U34.22
RXLED34: LED70.C, U35.22
RXLED35: LED72.C, U36.22
RXLED36: LED74.C, U37.22
RXLED37: LED76.C, U38.22
RXLED38: LED78.C, U39.22
RXLED39: LED80.C, U40.22
RXLED40: LED82.C, U41.22
RXLED41: LED84.C, U42.22
RXLED42: LED86.C, U43.22
RXLED43: LED88.C, U44.22
RXLED44: LED90.C, U45.22
RXLED45: LED92.C, U46.22
RXLED46: LED94.C, U47.22
RXLED47: LED96.C, U48.22
RXLED48: LED98.C, U49.22
RXLED49: LED100.C, U50.22
TXLED: LED1.C, U1.23
TXLED1: LED3.C, U2.23
TXLED2: LED5.C, U3.23
TXLED3: LED7.C, U4.23
TXLED4: LED9.C, U5.23
TXLED5: LED11.C, U6.23
TXLED6: LED13.C, U7.23
TXLED7: LED15.C, U8.23
TXLED8: LED17.C, U9.23
TXLED9: LED19.C, U10.23
TXLED10: LED21.C, U11.23
TXLED11: LED23.C, U12.23
TXLED12: LED25.C, U13.23
TXLED13: LED27.C, U14.23
TXLED14: LED29.C, U15.23
TXLED15: LED31.C, U16.23
TXLED16: LED33.C, U17.23
TXLED17: LED35.C, U18.23
TXLED18: LED37.C, U19.23
TXLED19: LED39.C, U20.23
TXLED20: LED41.C, U21.23
TXLED21: LED43.C, U22.23
TXLED22: LED45.C, U23.23
TXLED23: LED47.C, U24.23
TXLED24: LED49.C, U25.23
TXLED25: LED51.C, U26.23
TXLED26: LED53.C, U27.23
TXLED27: LED55.C, U28.23
TXLED28: LED57.C, U29.23
TXLED29: LED59.C, U30.23
TXLED30: LED61.C, U31.23
TXLED31: LED63.C, U32.23
TXLED32: LED65.C, U33.23
TXLED33: LED67.C, U34.23
TXLED34: LED69.C, U35.23
TXLED35: LED71.C, U36.23
TXLED36: LED73.C, U37.23
TXLED37: LED75.C, U38.23
TXLED38: LED77.C, U39.23
TXLED39: LED79.C, U40.23
TXLED40: LED81.C, U41.23
TXLED41: LED83.C, U42.23
TXLED42: LED85.C, U43.23
TXLED43: LED87.C, U44.23
TXLED44: LED89.C, U45.23
TXLED45: LED91.C, U46.23
TXLED46: LED93.C, U47.23
TXLED47: LED95.C, U48.23
TXLED48: LED97.C, U49.23
TXLED49: LED99.C, U50.23
TXO: JP1.4, U1.1
TXO1: JP8.4, U2.1
TXO2: JP14.4, U3.1
TXO3: JP20.4, U4.1
TXO4: JP26.4, U5.1
TXO5: JP32.4, U6.1
TXO6: JP38.4, U7.1
TXO7: JP44.4, U8.1
TXO8: JP50.4, U9.1
TXO9: JP56.4, U10.1
TXO10: JP62.4, U11.1
TXO11: JP68.4, U12.1
TXO12: JP74.4, U13.1
TXO13: JP80.4, U14.1
TXO14: JP86.4, U15.1
TXO15: JP92.4, U16.1
TXO16: JP98.4, U17.1
TXO17: JP104.4, U18.1
TXO18: JP110.4, U19.1
TXO19: JP116.4, U20.1
TXO20: JP122.4, U21.1
TXO21: JP128.4, U22.1
TXO22: JP134.4, U23.1
TXO23: JP140.4, U24.1
TXO24: JP146.4, U25.1
TXO25: JP152.4, U26.1
TXO26: JP158.4, U27.1
TXO27: JP164.4, U28.1
TXO28: JP170.4, U29.1
TXO29: JP176.4, U30.1
TXO30: JP182.4, U31.1
TXO31: JP188.4, U32.1
TXO32: JP194.4, U33.1
TXO33: JP200.4, U34.1
TXO34: JP206.4, U35.1
TXO35: JP212.4, U36.1
TXO36: JP218.4, U37.1
TXO37: JP224.4, U38.1
TXO38: JP230.4, U39.1
TXO39: JP236.4, U40.1
TXO40: JP242.4, U41.1
TXO41: JP248.4, U42.1
TXO42: JP254.4, U43.1
TXO43: JP260.4, U44.1
TXO44: JP266.4, U45.1
TXO45: JP272.4, U46.1
TXO46: JP278.4, U47.1
TXO47: JP284.4, U48.1
TXO48: JP290.4, U49.1
TXO49: JP296.4, U50.1
USB_D+: U1.15, X2.D+
USB_D+1: U2.15, X1.D+
USB_D+2: U3.15, X3.D+
USB_D+3: U4.15, X4.D+
USB_D+4: U5.15, X5.D+
USB_D+5: U6.15, X6.D+
USB_D+6: U7.15, X7.D+
USB_D+7: U8.15, X8.D+
USB_D+8: U9.15, X9.D+
USB_D+9: U10.15, X10.D+
USB_D+10: U11.15, X11.D+
USB_D+11: U12.15, X12.D+
USB_D+12: U13.15, X13.D+
USB_D+13: U14.15, X14.D+
USB_D+14: U15.15, X15.D+
USB_D+15: U16.15, X16.D+
USB_D+16: U17.15, X17.D+
USB_D+17: U18.15, X18.D+
USB_D+18: U19.15, X19.D+
USB_D+19: U20.15, X20.D+
USB_D+20: U21.15, X21.D+
USB_D+21: U22.15, X22.D+
USB_D+22: U23.15, X23.D+
USB_D+23: U24.15, X24.D+
USB_D+24: U25.15, X25.D+
USB_D+25: U26.15, X26.D+
USB_D+26: U27.15, X27.D+
USB_D+27: U28.15, X28.D+
USB_D+28: U29.15, X29.D+
USB_D+29: U30.15, X30.D+
USB_D+30: U31.15, X31.D+
USB_D+31: U32.15, X32.D+
USB_D+32: U33.15, X33.D+
USB_D+33: U34.15, X34.D+
USB_D+34: U35.15, X35.D+
USB_D+35: U36.15, X36.D+
USB_D+36: U37.15, X37.D+
USB_D+37: U38.15, X38.D+
USB_D+38: U39.15, X39.D+
USB_D+39: U40.15, X40.D+
USB_D+40: U41.15, X41.D+
USB_D+41: U42.15, X42.D+
USB_D+42: U43.15, X43.D+
USB_D+43: U44.15, X44.D+
USB_D+44: U45.15, X45.D+
USB_D+45: U46.15, X46.D+
USB_D+46: U47.15, X47.D+
USB_D+47: U48.15, X48.D+
USB_D+48: U49.15, X49.D+
USB_D+49: U50.15, X50.D+
USB_D-: U1.16, X2.D-
USB_D-1: U2.16, X1.D-
USB_D-2: U3.16, X3.D-
USB_D-3: U4.16, X4.D-
USB_D-4: U5.16, X5.D-
USB_D-5: U6.16, X6.D-
USB_D-6: U7.16, X7.D-
USB_D-7: U8.16, X8.D-
USB_D-8: U9.16, X9.D-
USB_D-9: U10.16, X10.D-
USB_D-10: U11.16, X11.D-
USB_D-11: U12.16, X12.D-
USB_D-12: U13.16, X13.D-
USB_D-13: U14.16, X14.D-
USB_D-14: U15.16, X15.D-
USB_D-15: U16.16, X16.D-
USB_D-16: U17.16, X17.D-
USB_D-17: U18.16, X18.D-
USB_D-18: U19.16, X19.D-
USB_D-19: U20.16, X20.D-
USB_D-20: U21.16, X21.D-
USB_D-21: U22.16, X22.D-
USB_D-22: U23.16, X23.D-
USB_D-23: U24.16, X24.D-
USB_D-24: U25.16, X25.D-
USB_D-25: U26.16, X26.D-
USB_D-26: U27.16, X27.D-
USB_D-27: U28.16, X28.D-
USB_D-28: U29.16, X29.D-
USB_D-29: U30.16, X30.D-
USB_D-30: U31.16, X31.D-
USB_D-31: U32.16, X32.D-
USB_D-32: U33.16, X33.D-
USB_D-33: U34.16, X34.D-
USB_D-34: U35.16, X35.D-
USB_D-35: U36.16, X36.D-
USB_D-36: U37.16, X37.D-
USB_D-37: U38.16, X38.D-
USB_D-38: U39.16, X39.D-
USB_D-39: U40.16, X40.D-
USB_D-40: U41.16, X41.D-
USB_D-41: U42.16, X42.D-
USB_D-42: U43.16, X43.D-
USB_D-43: U44.16, X44.D-
USB_D-44: U45.16, X45.D-
USB_D-45: U46.16, X46.D-
USB_D-46: U47.16, X47.D-
USB_D-47: U48.16, X48.D-
USB_D-48: U49.16, X49.D-
USB_D-49: U50.16, X50.D-

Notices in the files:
parts and their libraries:
SparkFun-Aesthetics: Licensing: CC v3.0 Share-Alike You are welcome to use this library for commercial purposes.
SparkFun-Aesthetics: Released under the Creative Commons Attribution Share-Alike 3.0 License
SparkFun-Aesthetics: http://creativecommons.org/licenses/by-sa/3.0
